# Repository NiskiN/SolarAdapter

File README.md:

# SolarAdapter
A simple adapter to connect between USB and the SCIC connector onboard the EnduroSat 1U Solar Panels

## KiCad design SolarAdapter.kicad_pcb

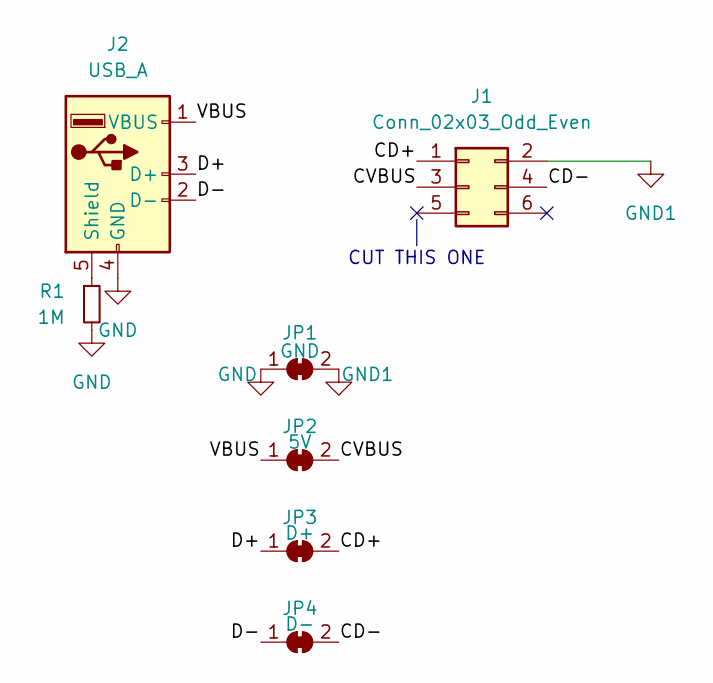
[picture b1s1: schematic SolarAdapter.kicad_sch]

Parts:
J1: Conn_02x03_Odd_Even; SAMTEC_TMS-103-01-L-D-RA; MPN FTSH-103-04-L-DH
J2: USB_A; USB_A_CONNFLY_DS1095-WNR0; MPN 6364372-2
JP1: GND; SolderJumper-2_P1.3mm_Bridged_RoundedPad1.0x1.5mm
JP2: 5V; SolderJumper-2_P1.3mm_Bridged_RoundedPad1.0x1.5mm
JP3: D+; SolderJumper-2_P1.3mm_Bridged_RoundedPad1.0x1.5mm
JP4: D-; SolderJumper-2_P1.3mm_Bridged_RoundedPad1.0x1.5mm
R1: 1M; R_0603_1608Metric; MPN ERJ-PA3F1004V

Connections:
/CD+: J1.1, JP3.2 (B)
/CD-: J1.4, JP4.2 (B)
/CVBUS: J1.3, JP2.2 (B)
/D+: J2.3 (D+), JP3.1 (A)
/D-: J2.2 (D-), JP4.1 (A)
/VBUS: J2.1 (VBUS), JP2.1 (A)
GND: J2.4 (GND), JP1.1 (A), R1.2
GND1: J1.2, JP1.2 (B)
unnamed: J2.5 (Shield), R1.1

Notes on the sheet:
CUT THIS ONE

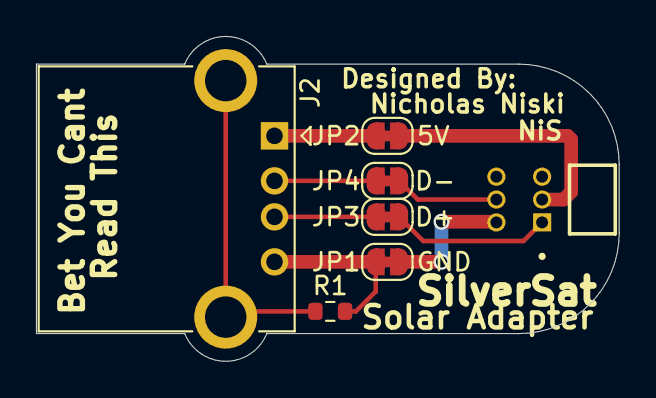
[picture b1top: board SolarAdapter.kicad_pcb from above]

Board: 2 copper layers, 32.4 x 18.0 mm, 7 parts (0 on the bottom side), 9 nets.

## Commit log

2024-10-13 Solar Adapter V1.0.0
    Release of Solar Adapter, an adapter from SCIC(EnduroSat Solar Panel Connector) to USB
    Release Notes:
    1. Released Solar Adapter. Not much else to say
2024-10-17 Solar Adapter 1.1
    Release Notes:
    1. Added MPNs to parts(whoops)
    2. Beefed up power traces to allow for higher current draws
2024-10-19 Solar Adapter 1.1.1
    Patch Notes:
    1. Original connector was too short, so it was replaced with a longer connector
